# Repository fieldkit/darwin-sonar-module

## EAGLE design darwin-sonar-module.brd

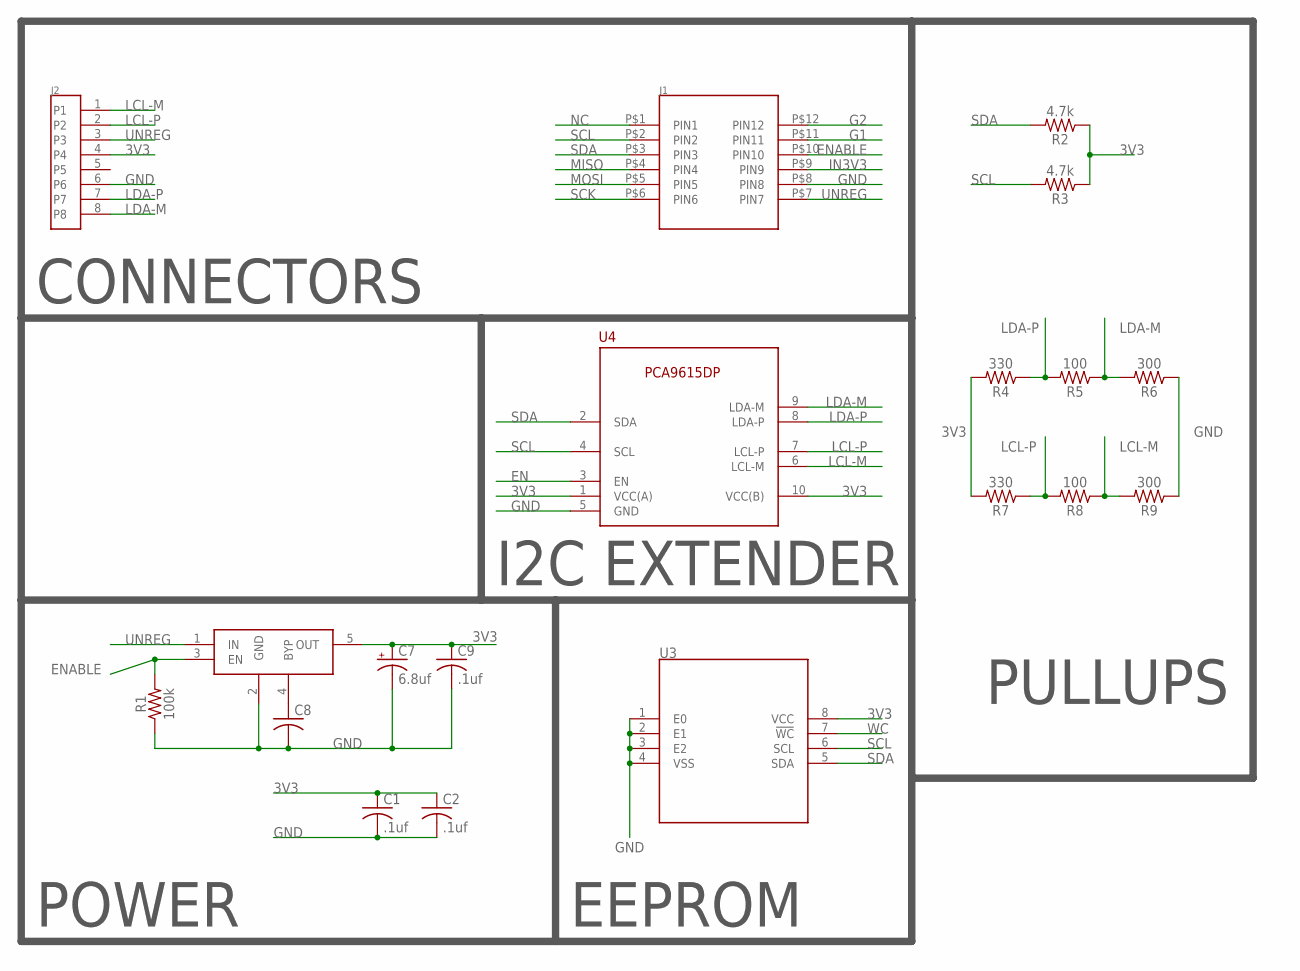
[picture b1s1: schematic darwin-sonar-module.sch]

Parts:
C1, C2, C9: .1uf; C0603K
C7: 6.8uf; A/3216-18R
C8: C-USC0603K; C0603K
J1: 2X6-HEADERS; M20-7810645
J2: 95501-6889VERT; 85513-5009
R1: 100k; 0603
R2, R3: 4.7k; 0603
R4, R7: 330; 0603
R5, R8: 100; 0603
R6, R9: 300; 0603
U3: M24C02-WMN6TP; SOIC127P600X175-8
U4: PCA9615; SOP50P490X110-10
U$4: MIC5219-3.3YM5-TR; SOT95P280X145-5

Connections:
3V3: C1.1, C2.1, C7.+, C9.1, J2.4, R2.1, R3.1, R4.2, R7.2, U3.8 (VCC), U4.1 (VCC(A)), U4.10 (VCC(B)), U$4.5 (OUT)
EN: U4.3 (EN)
ENABLE: J1.P$10 (PIN10), R1.2, U$4.3 (EN)
G1: J1.P$11 (PIN11)
G2: J1.P$12 (PIN12)
GND: C1.2, C2.2, C7.-, C8.2, C9.2, J1.P$8 (PIN8), J2.6, R1.1, R6.1, R9.1, U3.1 (E0), U3.2 (E1), U3.3 (E2), U3.4 (VSS), U4.5 (GND), U$4.2 (GND)
IN3V3: J1.P$9 (PIN9)
LCL-M: J2.1, R8.1, R9.2, U4.6 (LCL-M)
LCL-P: J2.2, R7.1, R8.2, U4.7 (LCL-P)
LDA-M: J2.8, R5.1, R6.2, U4.9 (LDA-M)
LDA-P: J2.7, R4.1, R5.2, U4.8 (LDA-P)
MISO: J1.P$4 (PIN4)
MOSI: J1.P$5 (PIN5)
unnamed: C8.1, U$4.4 (BYP)
NC: J1.P$1 (PIN1)
SCK: J1.P$6 (PIN6)
SCL: J1.P$2 (PIN2), R3.2, U3.6 (SCL), U4.4 (SCL)
SDA: J1.P$3 (PIN3), R2.2, U3.5 (SDA), U4.2 (SDA)
UNREG: J1.P$7 (PIN7), J2.3, U$4.1 (IN)
WC: U3.7 (!WC)

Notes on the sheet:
CONNECTORS
I2C EXTENDER
POWER
EEPROM
PULLUPS

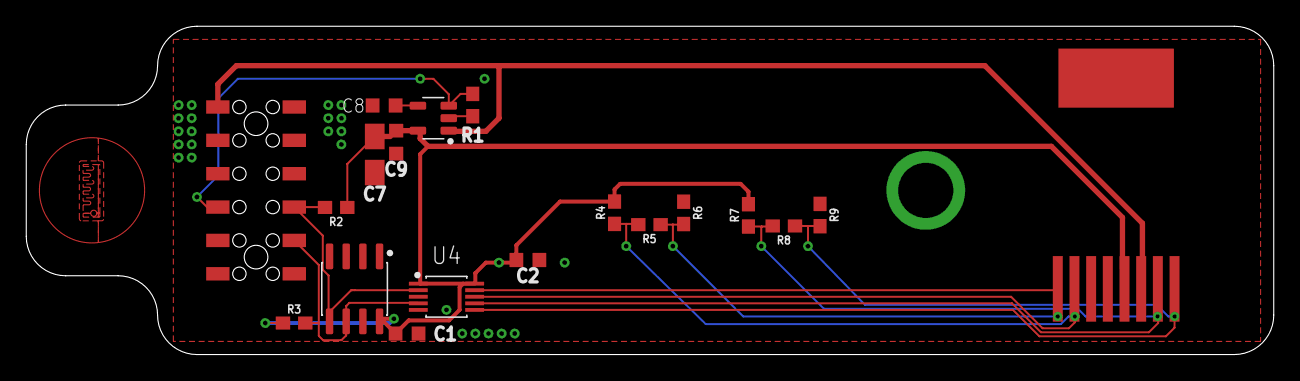
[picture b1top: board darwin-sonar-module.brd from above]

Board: 2 copper layers, 95.0 x 25.0 mm, 19 parts (0 on the bottom side), 11 nets.

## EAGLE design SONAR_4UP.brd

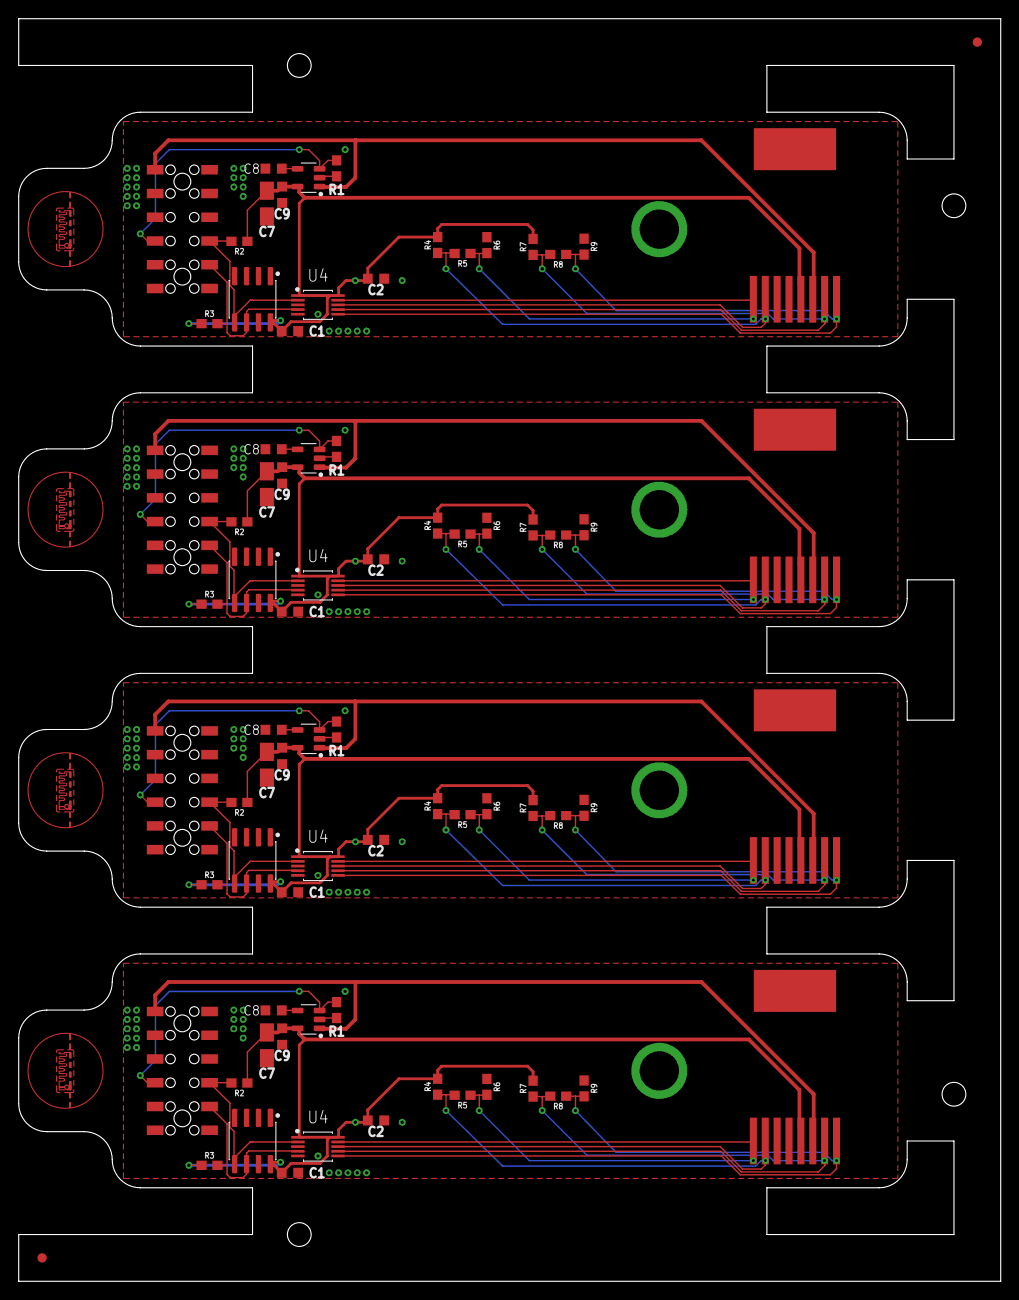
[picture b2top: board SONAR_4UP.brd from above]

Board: 2 copper layers, 105.0 x 135.0 mm, 78 parts (0 on the bottom side), 44 nets.

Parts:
C1, C2, C5, C6, C9, C10, C13, C14, C15, C18, C19, C20: .1uf; C0603K
C3, C7, C11, C16: 6.8uf; A/3216-18R
C4, C8, C12, C17: C0603K
FID1, FID13: FIDUCIAL_1MM
J1, J3, J5, J7: 2X6-HEADERS; M20-7810645
J2, J4, J6, J8: 95501-6889VERT; 85513-5009
R1, R10, R19, R28: 100k; 0603
R2, R3, R11, R12, R20, R21, R29, R30: 4.7k; 0603
R4, R7, R13, R16, R22, R25, R31, R34: 330; 0603
R5, R8, R14, R17, R23, R26, R32, R35: 100; 0603
R6, R9, R15, R18, R24, R27, R33, R36: 300; 0603
U1, U3, U5, U7: M24C02-WMN6TP; SOIC127P600X175-8
U2, U4, U6, U8: PCA9615; SOP50P490X110-10
U$1, U$2, U$3, U$4: MIC5219-3.3YM5-TR; SOT95P280X145-5

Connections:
3V1: C3.+, C5.1, C6.1, C10.1, J4.4, R11.1, R12.1, R13.2, R16.2, U1.8, U2.1, U2.10, U$1.5
3V2: C11.+, C13.1, C14.1, C15.1, J6.4, R20.1, R21.1, R22.2, R25.2, U5.8, U6.1, U6.10, U$2.5
3V3: C1.1, C2.1, C7.+, C9.1, J2.4, R2.1, R3.1, R4.2, R7.2, U3.8, U4.1, U4.10, U$4.5
3V4: C16.+, C18.1, C19.1, C20.1, J8.4, R29.1, R30.1, R31.2, R34.2, U7.8, U8.1, U8.10, U$3.5
ENABLE: J1.P$10, R1.2, U$4.3
ENABLE1: J3.P$10, R10.2, U$1.3
ENABLE2: J5.P$10, R19.2, U$2.3
ENABLE3: J7.P$10, R28.2, U$3.3
GND: C1.2, C2.2, C7.-, C8.2, C9.2, J1.P$8, J2.6, R1.1, R6.1, R9.1, U3.1, U3.2, U3.3, U3.4, U4.5, U$4.2
GND2: C3.-, C4.2, C5.2, C6.2, C10.2, J3.P$8, J4.6, R10.1, R15.1, R18.1, U1.1, U1.2, U1.3, U1.4, U2.5, U$1.2
GND4: C11.-, C12.2, C13.2, C14.2, C15.2, J5.P$8, J6.6, R19.1, R24.1, R27.1, U5.1, U5.2, U5.3, U5.4, U6.5, U$2.2
GND6: C16.-, C17.2, C18.2, C19.2, C20.2, J7.P$8, J8.6, R28.1, R33.1, R36.1, U7.1, U7.2, U7.3, U7.4, U8.5, U$3.2
LCL-M: J2.1, R8.1, R9.2, U4.6
LCL-M1: J4.1, R17.1, R18.2, U2.6
LCL-M2: J6.1, R26.1, R27.2, U6.6
LCL-M3: J8.1, R35.1, R36.2, U8.6
LCL-P: J2.2, R7.1, R8.2, U4.7
LCL-P1: J4.2, R16.1, R17.2, U2.7
LCL-P2: J6.2, R25.1, R26.2, U6.7
LCL-P3: J8.2, R34.1, R35.2, U8.7
LDA-M: J2.8, R5.1, R6.2, U4.9
LDA-M1: J4.8, R14.1, R15.2, U2.9
LDA-M2: J6.8, R23.1, R24.2, U6.9
LDA-M3: J8.8, R32.1, R33.2, U8.9
LDA-P: J2.7, R4.1, R5.2, U4.8
LDA-P1: J4.7, R13.1, R14.2, U2.8
LDA-P2: J6.7, R22.1, R23.2, U6.8
LDA-P3: J8.7, R31.1, R32.2, U8.8
unnamed: C4.1, U$1.4
unnamed: C12.1, U$2.4
unnamed: C8.1, U$4.4
unnamed: C17.1, U$3.4
SCL: J1.P$2, R3.2, U3.6, U4.4
SCL1: J3.P$2, R12.2, U1.6, U2.4
SCL2: J5.P$2, R21.2, U5.6, U6.4
SCL3: J7.P$2, R30.2, U7.6, U8.4
SDA: J1.P$3, R2.2, U3.5, U4.2
SDA1: J3.P$3, R11.2, U1.5, U2.2
SDA2: J5.P$3, R20.2, U5.5, U6.2
SDA3: J7.P$3, R29.2, U7.5, U8.2
UNREG: J1.P$7, J2.3, U$4.1
UNREG1: J3.P$7, J4.3, U$1.1
UNREG2: J5.P$7, J6.3, U$2.1
UNREG3: J7.P$7, J8.3, U$3.1

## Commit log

2020-01-16 Migrated to new footprint and added icon.

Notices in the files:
parts and their libraries:
SparkFun-Resistors: Licensing: Creative Commons ShareAlike 4.0 International - https://creativecommons.org/licenses/by-sa/4.0
